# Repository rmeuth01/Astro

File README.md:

# Astro: Jetson Nano Handheld

## Description
 
The Astro is an open-source gaming handheld based on the Jetson Nano single board computer.  It is designed with the goals of performance, ergonomics, and to be built using off the shelf components and 3D printed parts.  This was designed to fit my personal use case so there are some odd design choices, such as mono-only headphone output and lack of internal speaker.  

## Features

- Jetson Nano SOC
  - Quad-core ARM Cortex-A57 processor (Overclocked to 2.0 GHz)
  - NVIDIA Maxwell GPU with 128  CUDA cores
  - 4 GB LPDDR4
  - RTC Enabled with battery backup
- 800 x 480 (5:3 aspect ratio) display
- 10,000mAh battery, providing up to 6 hours of gameplay
- 5.0GHz IEEE 802.11b/g/n/ac wireless, Bluetooth 4.2
- Mono Audio Output via i2s MAX98357A audio amplifier
- Headphone jack
- USB 2.0 Host port, USB-C Charging Port
- Charging indicator
- 3D Printed housing and buttons.
- D-Pad, Action Buttons, Start, Select, Turbo and Hotkey buttons
- Dual stacked shoulder buttons (L, R, LZ, RZ)
- 2x switch analog sticks
- Mirrored controller PCBs with FFC cables based on ATMEGA32u4 internal USB 2.0 HID controller
- Size: 220mm x 121mm x 40mm, Weight: 639.5g (she chonky)
- Adjustable TDP: 5W, 10W Modes
- Safe software/hardware shutdown to prevent corruption to the SD card data (low voltage shutdown included)
- ARES Operating System ( https://techtoytinker.com/nvidia-jetson-nano )

### Credits

- Astro Designed and Built by Ryan Meuth (rmeuth01 / beernalytic / DocRobot)
- Controller Design and software based on Retro Lite CM4 by Dmcke5 and StonedEdge ( https://github.com/StonedEdge/Retro-Lite-CM4 )

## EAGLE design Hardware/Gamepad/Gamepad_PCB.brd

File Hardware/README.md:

# Astro Hardware
The hardware consists of mostly off-the-shelf components, [custom gamepad](Gamepad/), and 3D printed [housing](Housing/) and [buttons](Buttons/).  The 3D printed parts are designed to be easily printed on a mid-range consumer 3D printer like an Ender 3 or similar. Design files are availble in this folder, and STL files are available on [Printables](https://www.printables.com/model/537843-astro-jetson-nano-game-handheld).  
The off-the shelf components are listed in the table below.

| Item	| Vendor / Link	| Qty |	Unit Cost |	Line Total |
| --- | --- | --- | --- | --- |
| Jetson Nano 4GB | [Sparkfun](https://www.sparkfun.com/products/16271) | 1 | $149.00 |	$149.00 |
| 10Ah Battery Pack | [Sparkfun](https://www.sparkfun.com/products/15593) | 1	| $21.50 |	$21.50 |
| 5" Screen - 800 x 480 |	[Adafruit](https://www.adafruit.com/product/1680) | 1 |	$29.95 | $29.95 |
| Soft Tactile Buttons |	[Adafruit](https://www.adafruit.com/product/3101) |	1 | $1.95 |	$1.95 |
| i2s Audio Amplifier |	[Adafruit](https://www.adafruit.com/product/3006) |	1 |	$5.95 |	$5.95 |
| Power switch |	[Adafruit](https://www.adafruit.com/product/805) | 1	| $0.95 |	$0.95 |
| HDMI to TTL Board |	[Adafruit](https://www.adafruit.com/product/2218) |	1	| $29.95 |	$29.95 |
| DIY HDMI Straight |	[Adafruit](https://www.adafruit.com/product/3548) |	2 |	$6.50 |	$13.00 |
| DIY HDMI Ribbon Cable - 20cm | [Adafruit](https://www.adafruit.com/product/3561) | 1 | $1.95 |	$1.95 |
| SNES Rubber Kit |	[Console5](https://console5.com/store/snes-replacement-controller-silicone-rubber-carbon-dot-pads.html) |	2 |	$2.99 |	$5.98 |
| Switch Joysticks |	[Amazon](https://www.amazon.com/Replacement-Joystick-Nintendo-Original-Professional/dp/B08397JQZG/ref=sr_1_4?keywords=switch+joystick&qid=1675556877&s=electronics&sr=1-4) |	1 |	$8.99 |	$8.99 |
| Wifi / BT M.2 Module (Intel 8265) |	[Amazon](https://www.amazon.com/Intel-Dual-Band-Wireless-Ac-8265/dp/B01MZA1AB2/ref=sr_1_3_mod_primary_new?crid=1VYJ1K5ZFTBFY&keywords=intel+8265&qid=1667484760&qu=eyJxc2MiOiIyLjY1IiwicXNhIjoiMi4xNyIsInFzcCI6IjIuMTUifQ%3D%3D&s=electronics&sbo=RZvfv%2F%2FHxDF%2BO5021pAnSA%3D%3D&sprefix=intel+8265%2Celectronics%2C132&sr=1-3) |	1	| $19.95 |	$19.95 |
| Wifi / BT Antenna (x2) |	[Digikey](https://www.digikey.com/en/products/detail/molex/2042811100/8020427?s=N4IgTCBcDaILYHsA2BTAHgAjABgCxgA4BGE7bEAXQF8g) |	2 | $2.72 |	$5.44 |
| Custom Gamepad | https://jlcpcb.com/ | 1 | $40.00 | $40.00 |

Approx. Total: $335

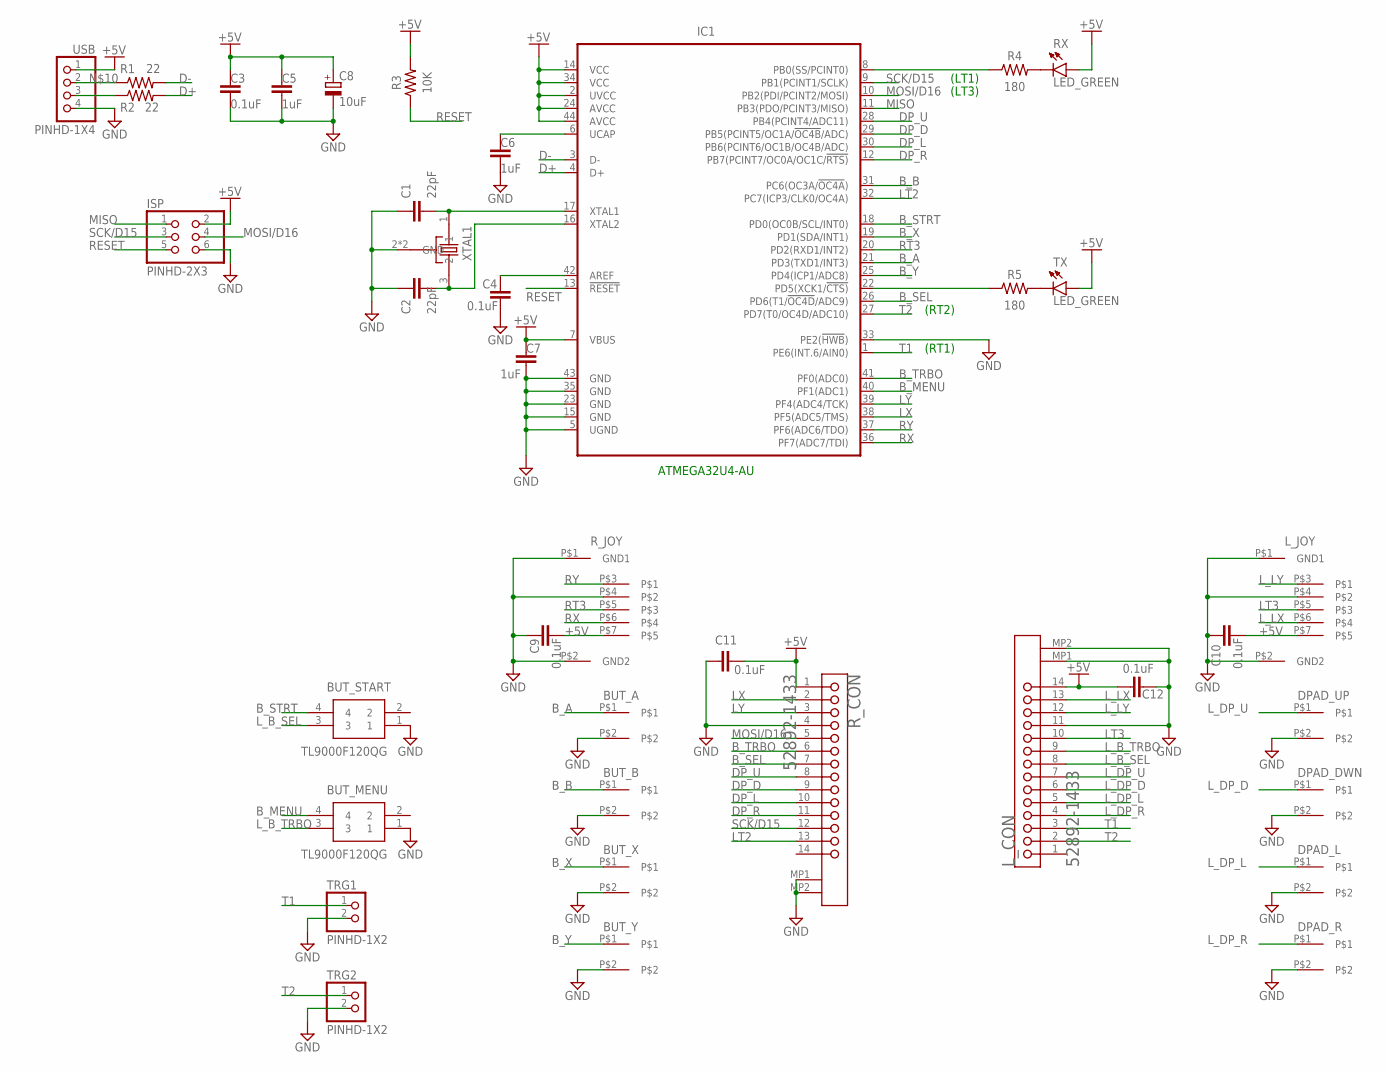
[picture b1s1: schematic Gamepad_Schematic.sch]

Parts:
BUT_A: MEMBRANEBUTTON
BUT_B: MEMBRANEBUTTON
BUT_MENU: TL9000F120QG
BUT_START: TL9000F120QG
BUT_X: MEMBRANEBUTTON
BUT_Y: MEMBRANEBUTTON
C1, C2: 22pF; CAPC1608X85
C3, C4, C9, C10, C11, C12: 0.1uF; CAPC2012X110
C5, C6, C7: 1uF; CAPC2012X110
C8: 10uF; CAPMP3216X180N
DPAD_DWN: MEMBRANEBUTTON
DPAD_L: MEMBRANEBUTTON
DPAD_R: MEMBRANEBUTTON
DPAD_UP: MEMBRANEBUTTON
IC1: ATMEGA32U4-AU; QFP80P1200X1200X120-44; MPN ATmega32U4-AU
ISP: PINHD-2X3; 2X03
L_CON: MOLEX_52892-1433MOLEX_52892-1433_0_0; MOLEX_52892-1433_0
L_JOY: 0545500571
R1, R2: 22; RESC2012X65
R3: 10K; RESC2012X65
R4, R5: 180; RESC2012X65
RX: LED_GREEN; LEDC1608X55N_FLAT-G
R_CON: MOLEX_52892-1433MOLEX_52892-1433_0_0; MOLEX_52892-1433_0
R_JOY: 0545500571
TRG1, TRG2: PINHD-1X2; 1X02
TX: LED_GREEN; LEDC1608X55N_FLAT-G
USB: PINHD-1X4; 1X04
XTAL1: ABM3BDIAG; OSCCC500X320X110

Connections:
+5V: C3.1, C5.1, C7.1, C8.1 (+), C9.2, C10.2, C11.2, C12.2, IC1.2 (UVCC), IC1.7 (VBUS), IC1.14 (VCC), IC1.24 (AVCC), IC1.34 (VCC), IC1.44 (AVCC), ISP.2, L_CON.14, L_JOY.P$7, R3.2, RX.A, R_CON.1, R_JOY.P$7, TX.A, USB.1
B_A: BUT_A.P$1, IC1.21 (PD3(TXD1/INT3))
B_B: BUT_B.P$1, IC1.31 (PC6(OC3A/!OC4A!))
B_MENU: BUT_MENU.4, IC1.40 (PF1(ADC1))
B_SEL: IC1.26 (PD6(T1/!OC4D!/ADC9)), R_CON.7
B_STRT: BUT_START.4, IC1.18 (PD0(OC0B/SCL/INT0))
B_TRBO: IC1.41 (PF0(ADC0)), R_CON.6
B_X: BUT_X.P$1, IC1.19 (PD1(SDA/INT1))
B_Y: BUT_Y.P$1, IC1.25 (PD4(ICP1/ADC8))
D+: IC1.4 (D+), R2.2
D-: IC1.3 (D-), R1.2
DP_D: IC1.29 (PB5(PCINT5/OC1A/!OC4B!/ADC)), R_CON.9
DP_L: IC1.30 (PB6(PCINT6/OC1B/OC4B/ADC)), R_CON.10
DP_R: IC1.12 (PB7(PCINT7/OC0A/OC1C/!RTS)), R_CON.11
DP_U: IC1.28 (PB4(PCINT4/ADC11)), R_CON.8
GND: BUT_A.P$2, BUT_B.P$2, BUT_MENU.1, BUT_START.1, BUT_X.P$2, BUT_Y.P$2, C1.1, C2.1, C3.2, C4.2, C5.2, C6.2, C7.2, C8.2 (-), C9.1, C10.1, C11.1, C12.1, DPAD_DWN.P$2, DPAD_L.P$2, DPAD_R.P$2, DPAD_UP.P$2, IC1.5 (UGND), IC1.15 (GND), IC1.23 (GND), IC1.33 (PE2(!HWB!)), IC1.35 (GND), IC1.43 (GND), ISP.6, L_CON.11, L_CON.MP1, L_CON.MP2, L_JOY.P$1 (GND1), L_JOY.P$2 (GND2), L_JOY.P$4, R_CON.4, R_CON.MP1, R_CON.MP2, R_JOY.P$1 (GND1), R_JOY.P$2 (GND2), R_JOY.P$4, TRG1.2, TRG2.2, USB.4, XTAL1.2 (GND), XTAL1.4 (GND)
LT2: IC1.32 (PC7(ICP3/CLK0/OC4A)), R_CON.13
LT3: L_CON.10, L_JOY.P$5
LX: IC1.38 (PF5(ADC5/TMS)), R_CON.2
LY: IC1.39 (PF4(ADC4/TCK)), R_CON.3
L_B_SEL: BUT_START.3, L_CON.8
L_B_TRBO: BUT_MENU.3, L_CON.9
L_DP_D: DPAD_DWN.P$1, L_CON.6
L_DP_L: DPAD_L.P$1, L_CON.5
L_DP_R: DPAD_R.P$1, L_CON.4
L_DP_U: DPAD_UP.P$1, L_CON.7
L_LX: L_CON.13, L_JOY.P$6
L_LY: L_CON.12, L_JOY.P$3
MISO: IC1.11 (PB3(PDO/PCINT3/MISO)), ISP.1
MOSI/D16: IC1.10 (PB2(PDI/PCINT2/MOSI)), ISP.4, R_CON.5
unnamed: C1.2, IC1.17 (XTAL1), XTAL1.1
unnamed: C6.1, IC1.6 (UCAP)
unnamed: R2.1, USB.3
unnamed: C2.2, IC1.16 (XTAL2), XTAL1.3 (2)
unnamed: C4.1, IC1.42 (AREF)
unnamed: R4.2, RX.C
unnamed: R5.2, TX.C
unnamed: IC1.8 (PB0(SS/PCINT0)), R4.1
unnamed: IC1.22 (PD5(XCK1/!CTS)), R5.1
unnamed: R1.1, USB.2
RESET: IC1.13 (!RESET), ISP.5, R3.1
RT3: IC1.20 (PD2(RXD1/INT2)), R_JOY.P$5
RX: IC1.36 (PF7(ADC7/TDI)), R_JOY.P$6
RY: IC1.37 (PF6(ADC6/TDO)), R_JOY.P$3
SCK/D15: IC1.9 (PB1(PCINT1/SCLK)), ISP.3, R_CON.12
T1: IC1.1 (PE6(INT.6/AIN0)), L_CON.3, TRG1.1
T2: IC1.27 (PD7(T0/OC4D/ADC10)), L_CON.2, TRG2.1

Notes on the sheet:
(LT1)
(LT3)
(RT1)
(RT2)

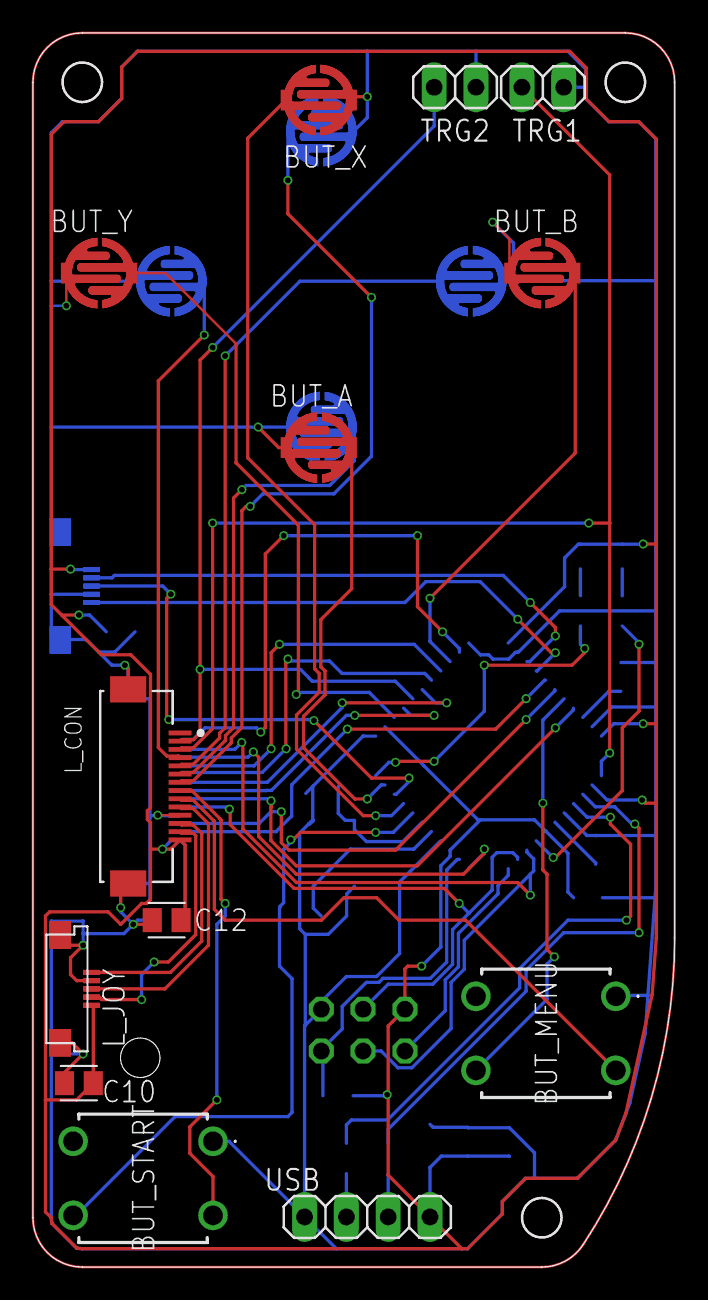
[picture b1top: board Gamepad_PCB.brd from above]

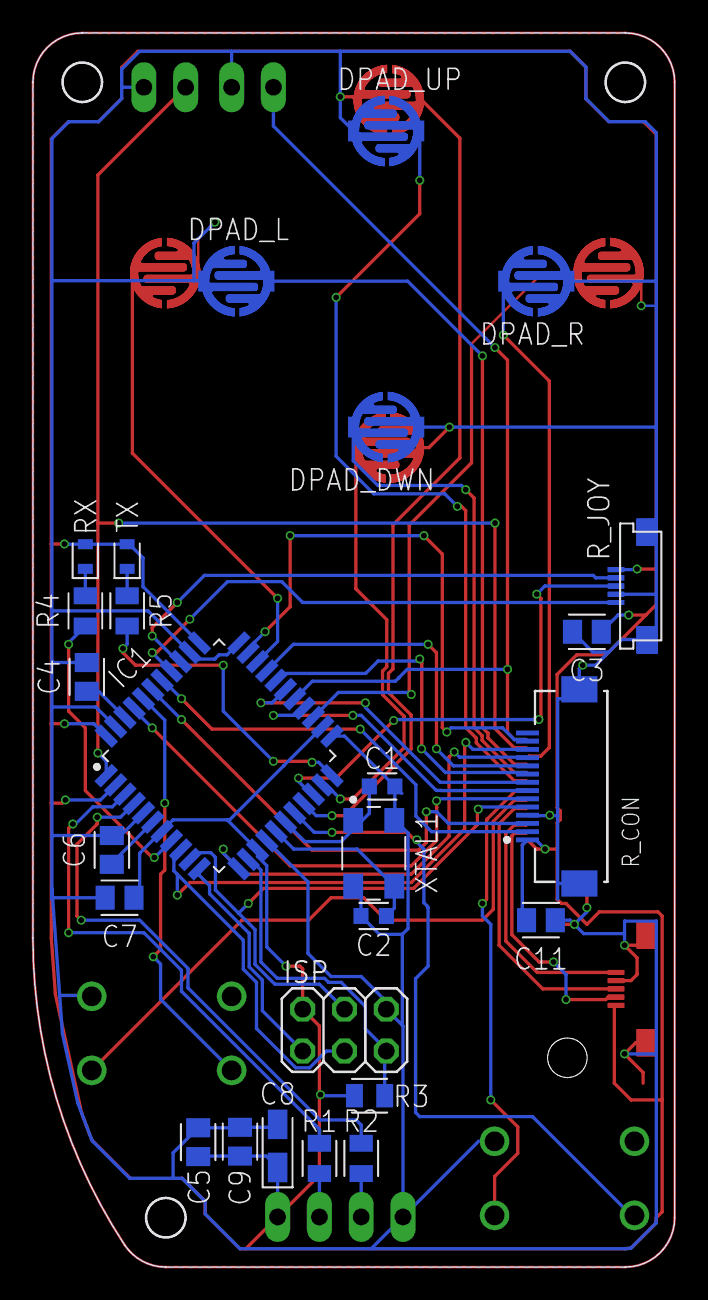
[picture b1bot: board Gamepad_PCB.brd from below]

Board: 2 copper layers, 39.0 x 75.0 mm, 39 parts (26 on the bottom side), 47 nets.

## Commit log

2023-06-24 Added Hardware and Software Notes
2023-06-25 Added Hardware and Software Files
2023-06-26 Added Front End Files
2023-07-28 Update Hardware README.md
    Added Off-the shelf BOM.
2023-07-30 Moved STL files to Printables.
